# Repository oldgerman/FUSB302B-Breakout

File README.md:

# FUSB302B-Breakout

## PCB

## Schematic

## B.O.M

 please see bom/ibom.html

## Relevant code

### Where does the code come from?

The code comes from the example of [Reclaimer Labs](https://www.reclaimerlabs.com/) shared by [GreatScott!](https://www.instructables.com/member/GreatScottLab/)

For more details, please see:

- [DIY_USB_Type-C_Power_Delivery_Trigger_Board](https://www.instructables.com/DIY-USB-Type-C-Power-Delivery-Trigger-Board/)
- [usb-c-arduino---graycatlabs](https://github.com/graycatlabs/usb-c-arduino)
- [USB-C-Explorer---ReclaimerLabs](https://github.com/ReclaimerLabs/USB-C-Explorer)

### Can I run this code on Arduino uno, nano, micro or leonardo?

No, they don't have enough SRAM(only 2KB)，It is recommended to use a processor with SRAM of 4KB and above

### How can I run this code with stm32 on arduino ide？

Well, please see [Arduino_Core_STM32](https://github.com/stm32duino/Arduino_Core_STM32)

### E.g. MCU

In theory, all MCUs supported by stm32duino support.

| MCU           | SRAM  | Has it been tested？ |
| ------------- | ----- | -------------------- |
| STM32F030F4P6 | 4KB   | :yellow_heart:       |
| STM32F072CBT6 | 16KB  | 💚                    |
| STM32F103C8T6 | 20KB  | :yellow_heart:       |
| ...           | ...   | ...                  |
| ESP8266       | 32KB? | 💚                    |

## Pictures

- The smallest system board used in the test is based on STM32F072CBT6, for more details, please see: [DarkPill](https://github.com/oldgerman/DarkPill)
- The PD charger used in test is XiaoMi AD651(65W), [report of disassembly](http://www.chongdiantou.com/wp/archives/46359.html)

<table>
    <td>
    <td>
    <td>
</table>

<table>
    <td>
    <td>
    <td>
</table>

## Acknowledgments

-  [GreatScott!](https://www.instructables.com/member/GreatScottLab/)
-  [Reclaimer Labs](https://www.reclaimerlabs.com/) 
- [STM32duino](https://github.com/stm32duino)

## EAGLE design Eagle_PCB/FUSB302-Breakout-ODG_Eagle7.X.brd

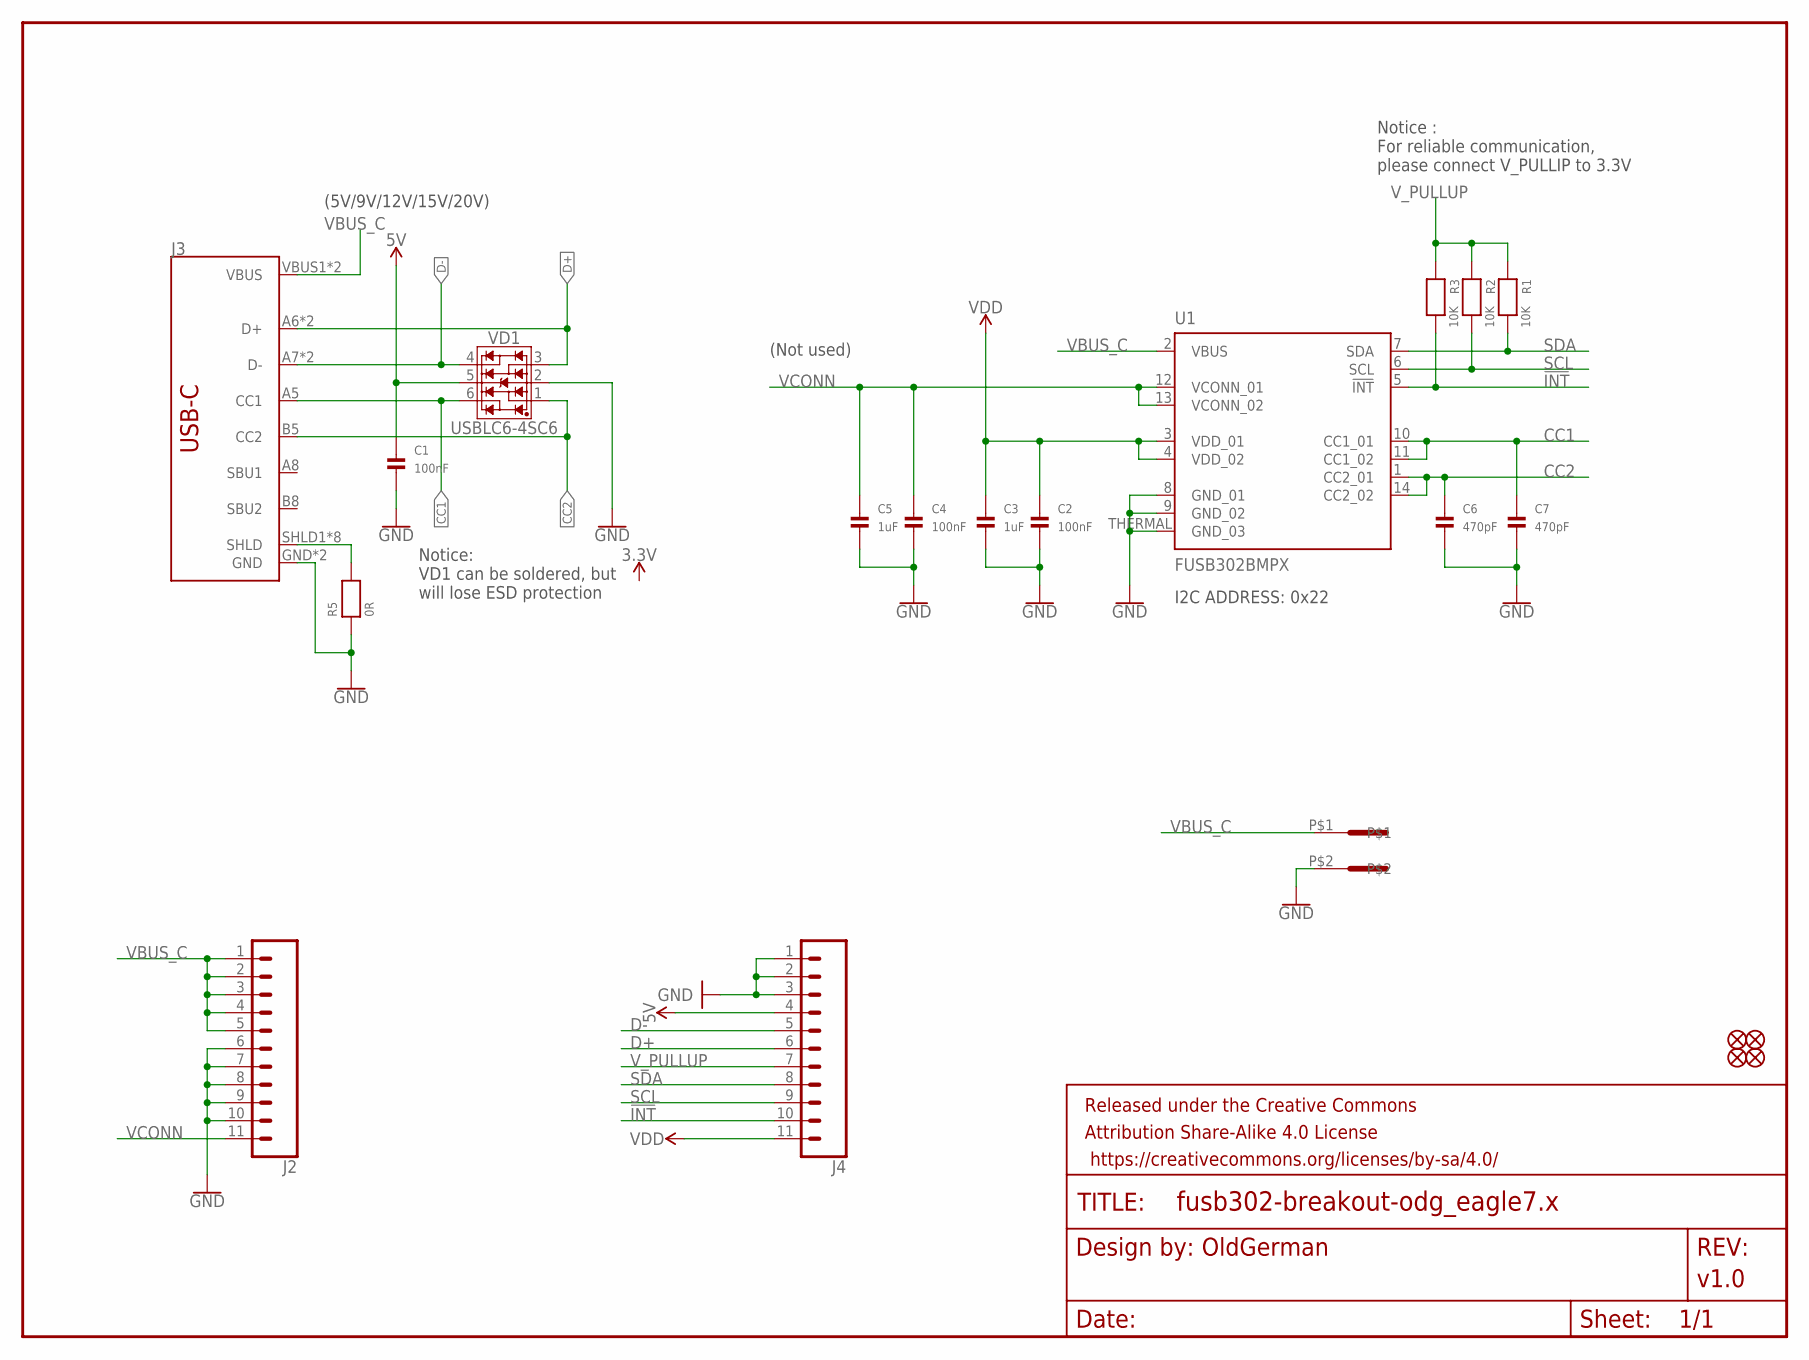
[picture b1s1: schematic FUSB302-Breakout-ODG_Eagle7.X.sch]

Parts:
C1, C2, C4: 100nF; 0603
C3, C5: 1uF; 0603
C6, C7: 470pF; 0603
FD5, FD6, FD7, FD8: FIDUCIAL_MINI1X2; FIDUCIAL-1X2
FRAME2: FRAME-LETTER; CREATIVE_COMMONS
J2, J4: CONN_11; 1X11
J3: USB_C_LONG-SYMBOL2-LAYER; USB-C-16P
R1, R2, R3: 10K; 0603
R5: 0R; 0603
U1: FUSB302BMPX; QFN14-2.5X2.5MM
U$5: 5.08MM_CONN; 1715250000
VD1: USBLC6-4SC6; SOT23-6

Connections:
5V: C1.1, J4.4, VD1.5
!INT: J4.10, R3.2, U1.5 (!INT)
CC1: C7.1, J3.A5 (CC1), U1.10 (CC1_01), U1.11 (CC1_02), VD1.6
CC2: C6.1, J3.B5 (CC2), U1.1 (CC2_01), U1.14 (CC2_02), VD1.1
D+: J3.A6 (D+), J3.B6 (D+), J4.6, VD1.3
D-: J3.A7 (D-), J3.B7 (D-), J4.5, VD1.4
GND: C1.2, C2.2, C3.2, C4.2, C5.2, C6.2, C7.2, J2.6, J2.7, J2.8, J2.9, J2.10, J3.GND, J3.GND2 (GND), J4.1, J4.2, J4.3, R5.1, U1.8 (GND_01), U1.9 (GND_02), U1.THERMAL (GND_03), U$5.P$2, VD1.2
unnamed: J3.SHLD1 (SHLD), J3.SHLD2 (SHLD), J3.SHLD3 (SHLD), J3.SHLD4 (SHLD), J3.SHLD5 (SHLD), J3.SHLD6 (SHLD), J3.SHLD7 (SHLD), J3.SHLD8 (SHLD), R5.2
SCL: J4.9, R2.2, U1.6 (SCL)
SDA: J4.8, R1.2, U1.7 (SDA)
VBUS_C: J2.1, J2.2, J2.3, J2.4, J2.5, J3.VBUS1 (VBUS), J3.VBUS2 (VBUS), U1.2 (VBUS), U$5.P$1
VCONN: C4.1, C5.1, J2.11, U1.12 (VCONN_01), U1.13 (VCONN_02)
VDD: C2.1, C3.1, J4.11, U1.3 (VDD_01), U1.4 (VDD_02)
V_PULLUP: J4.7, R1.1, R2.1, R3.1

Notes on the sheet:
I2C ADDRESS: 0x22
OldGerman
v1.0
Notice : For reliable communication, please connect V_PULLIP to 3.3V
(5V/9V/12V/15V/20V)
(Not used)
Notice: VD1 can be soldered, but will lose ESD protection

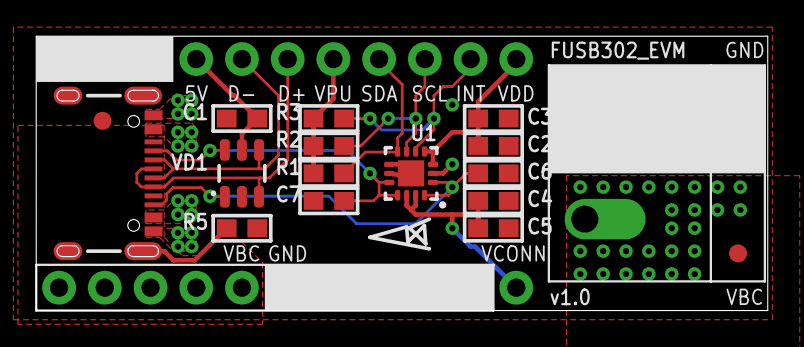
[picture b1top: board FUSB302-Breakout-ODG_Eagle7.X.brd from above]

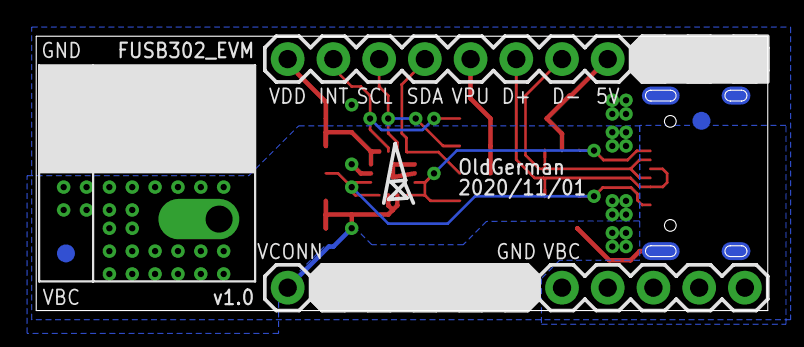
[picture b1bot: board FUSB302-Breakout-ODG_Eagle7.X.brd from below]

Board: 2 copper layers, 40.6 x 15.2 mm, 22 parts (4 on the bottom side), 14 nets.

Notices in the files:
parts and their libraries:
SparkFun-Connectors: Licensing: Creative Commons ShareAlike 4.0 International - https://creativecommons.org/licenses/by-sa/4.0
microbuilder: This work is placed in the public domain, and may be freely used for commercial and non-commercial work with the following conditions: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
